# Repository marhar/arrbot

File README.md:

arrbot
======

Software related to the arrbot project

Utilities
---------

arrterm -- wrapper for terminal-based tty connection to arduino board

ServoCalibrate -- find and save the center point of your servo

ServoTester -- test servos

Drivers
-------

(as in making the robot drive around, not device drivers)

treadtester -- first test for tread motion, just moves to and fro.

Setup
-----

For ServoCalibrate and ServoTester:

servo ground (black or brown): arduino GND
servo power (red):  arduino RAW
servo signal (white or yellow): arduino pin 9

For TreadTester:  left servo on 9, right servo on 10.

experiment stuff
----------------
- mpu6050 is at i2c address 0x68

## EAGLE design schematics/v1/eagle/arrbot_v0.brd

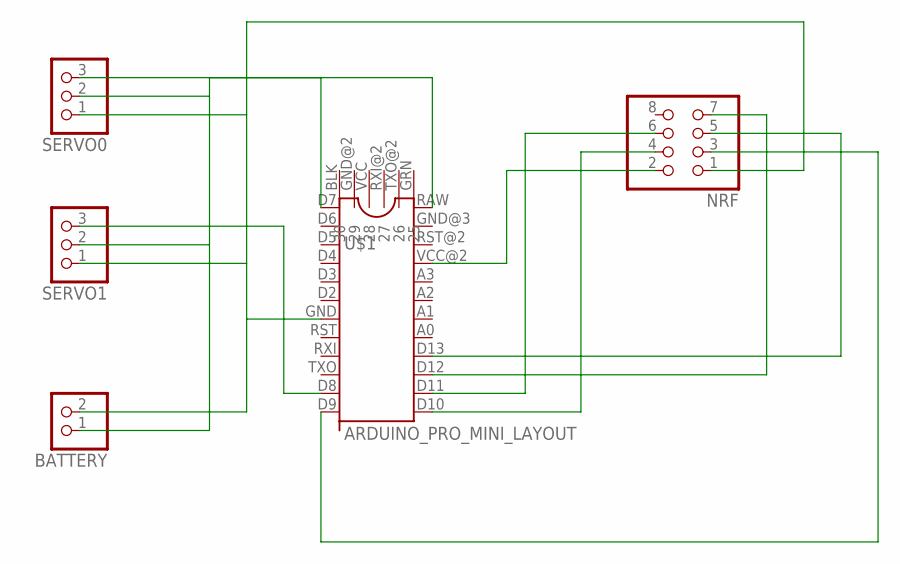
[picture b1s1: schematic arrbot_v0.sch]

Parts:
BATTERY: PINHD-1X2; 1X02
NRF: PINHD-2X4; 2X04
SERVO0, SERVO1: PINHD-1X3; 1X03
U$1: ARDUINO_PRO_MINI_LAYOUT; ARDUINO_PRO_MINI_PINOUT

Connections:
unnamed: BATTERY.2, NRF.1, SERVO0.1, SERVO1.1, U$1.GND (7)
unnamed: NRF.2, U$1.VCC@2 (21)
unnamed: NRF.3, U$1.D9 (12)
unnamed: NRF.4, U$1.D10 (13)
unnamed: NRF.5, U$1.D13 (16)
unnamed: NRF.6, U$1.D11 (14)
unnamed: NRF.7, U$1.D12 (15)
unnamed: BATTERY.1, SERVO0.2, SERVO1.2, U$1.RAW (24)
unnamed: SERVO0.3, U$1.D7 (1)
unnamed: SERVO1.3, U$1.D8 (11)

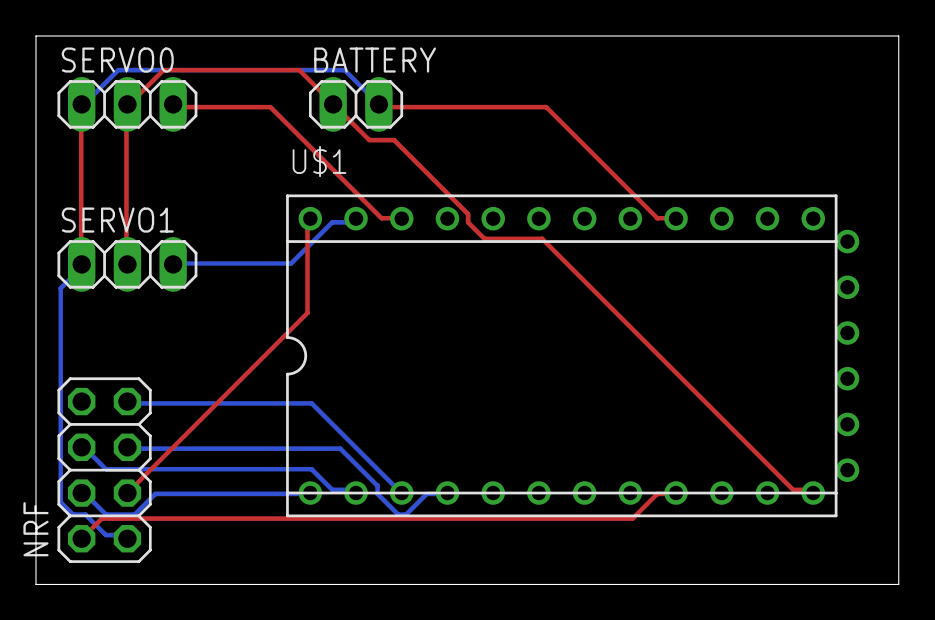
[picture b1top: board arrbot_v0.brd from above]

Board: 2 copper layers, 47.9 x 30.5 mm, 5 parts (0 on the bottom side), 10 nets.

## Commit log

2014-02-02 first cleaned up version.
2014-02-02 first addition, slightly modified from version downloaded.
2014-07-15 first try at servo calibrator. single servo, doesn't save state.
2014-07-19 Changed names to match typical Arduino naming, i.e. CamelCase w. init Caps.
    ServoCalibrator will (eventually) save to nonvolatile memory.
    ServoTester emulates the functionality of a standard 3-button servo tester.
    arrterm will connect to the arduino in a terminal window.
2014-07-19 ServoTester is ready. typo in arrterm.
2014-07-19 updated.
2014-07-21 first go at tread tester program.
2014-07-23 seems to be working. next step: integrate with calibrator.
2014-07-24 experimental main loop with periodic callouts.
2014-07-24 needs some work to figure out include paths. now relies on symlink to /arrbot. unwisely moved pgm files to CamelCase names. is that the right thing? added servo control and config header. maybe need 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
2014-07-24 renamed.
2014-07-24 catch renamed header files.
2014-08-01 first cut.
2014-08-02 Works. Need to add protection for not overwriting identical header.
2014-08-04 Getting ready to add physical servo logic, with calibrated percentage output. This current checkin guaranteed not to compile.
2014-08-06 renamed to arr_servocfg so we can create arr_servo that does real work.
2014-08-06 tidy up.
2014-08-06 added arrbot_servo which controls a calibrated servo.
2014-08-06 stty sane to clean up.
2014-08-06 Added (I think) servo reversing logic. Doesn't seem to work!
2014-08-09 first time.
2014-08-09 arduinoizing the include files.
2014-08-09 I think this is good for arduino libraries now.
2014-08-09 Added ArrNunchuck library.
2014-08-09 renamed to ArrNunchuck
2014-08-09 renamed members to be a bit more consistent.
2014-08-09 added an alternate init sequence. still not quite right, although works better on alonso's controller.
2014-08-11 oops, setting right reverse value properly.
2014-08-12 first nrf test, somewhat successful!
2014-08-16 standardized all baud rates to 9600. This will work with bluetooth and also with less powerful laptops that might have trouble scrolling at high rates.
2014-08-17 first cut -- lists whatever has changed in /dev/tty.*
2014-08-20 Starting on Nunchuck PC driver, based off of Nunchuck_Tester.
2014-08-20 gui for nunchuck. probably can obsolete some other nunchuck test programs.
2014-08-24 gui and cmd protocol now working.
2014-08-24 tidied up.
2014-08-29 This is the non-blinking version by Kurt.
2014-09-01 Tidied up print statements. Set ArrMote back to std init.
2014-09-02 Some convenient stuff.
2015-07-19 Thanks to clc@clcworld.net for the assist!
2015-07-20 Original rover files.
2015-07-20 composite thing files. objectname-printer-count.thing.
2015-07-20 for makerbot 2.
2015-07-28 state as of the final class
2015-07-28 experimental stuff while class was in session
2016-10-31 data entry program for battery resistance meter.
2019-04-22 Added AUTHORS as per Google guidelines.
2019-04-22 Create LICENSE
